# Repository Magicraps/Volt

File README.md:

# Volt
Vehicle Operations and Launch Telemetry - AerospaceNU's rocketry flight controller
https://github.com/AerospaceNU

Currently working on V1.
Open files in KiCAD. (I'm currently using V9.0)

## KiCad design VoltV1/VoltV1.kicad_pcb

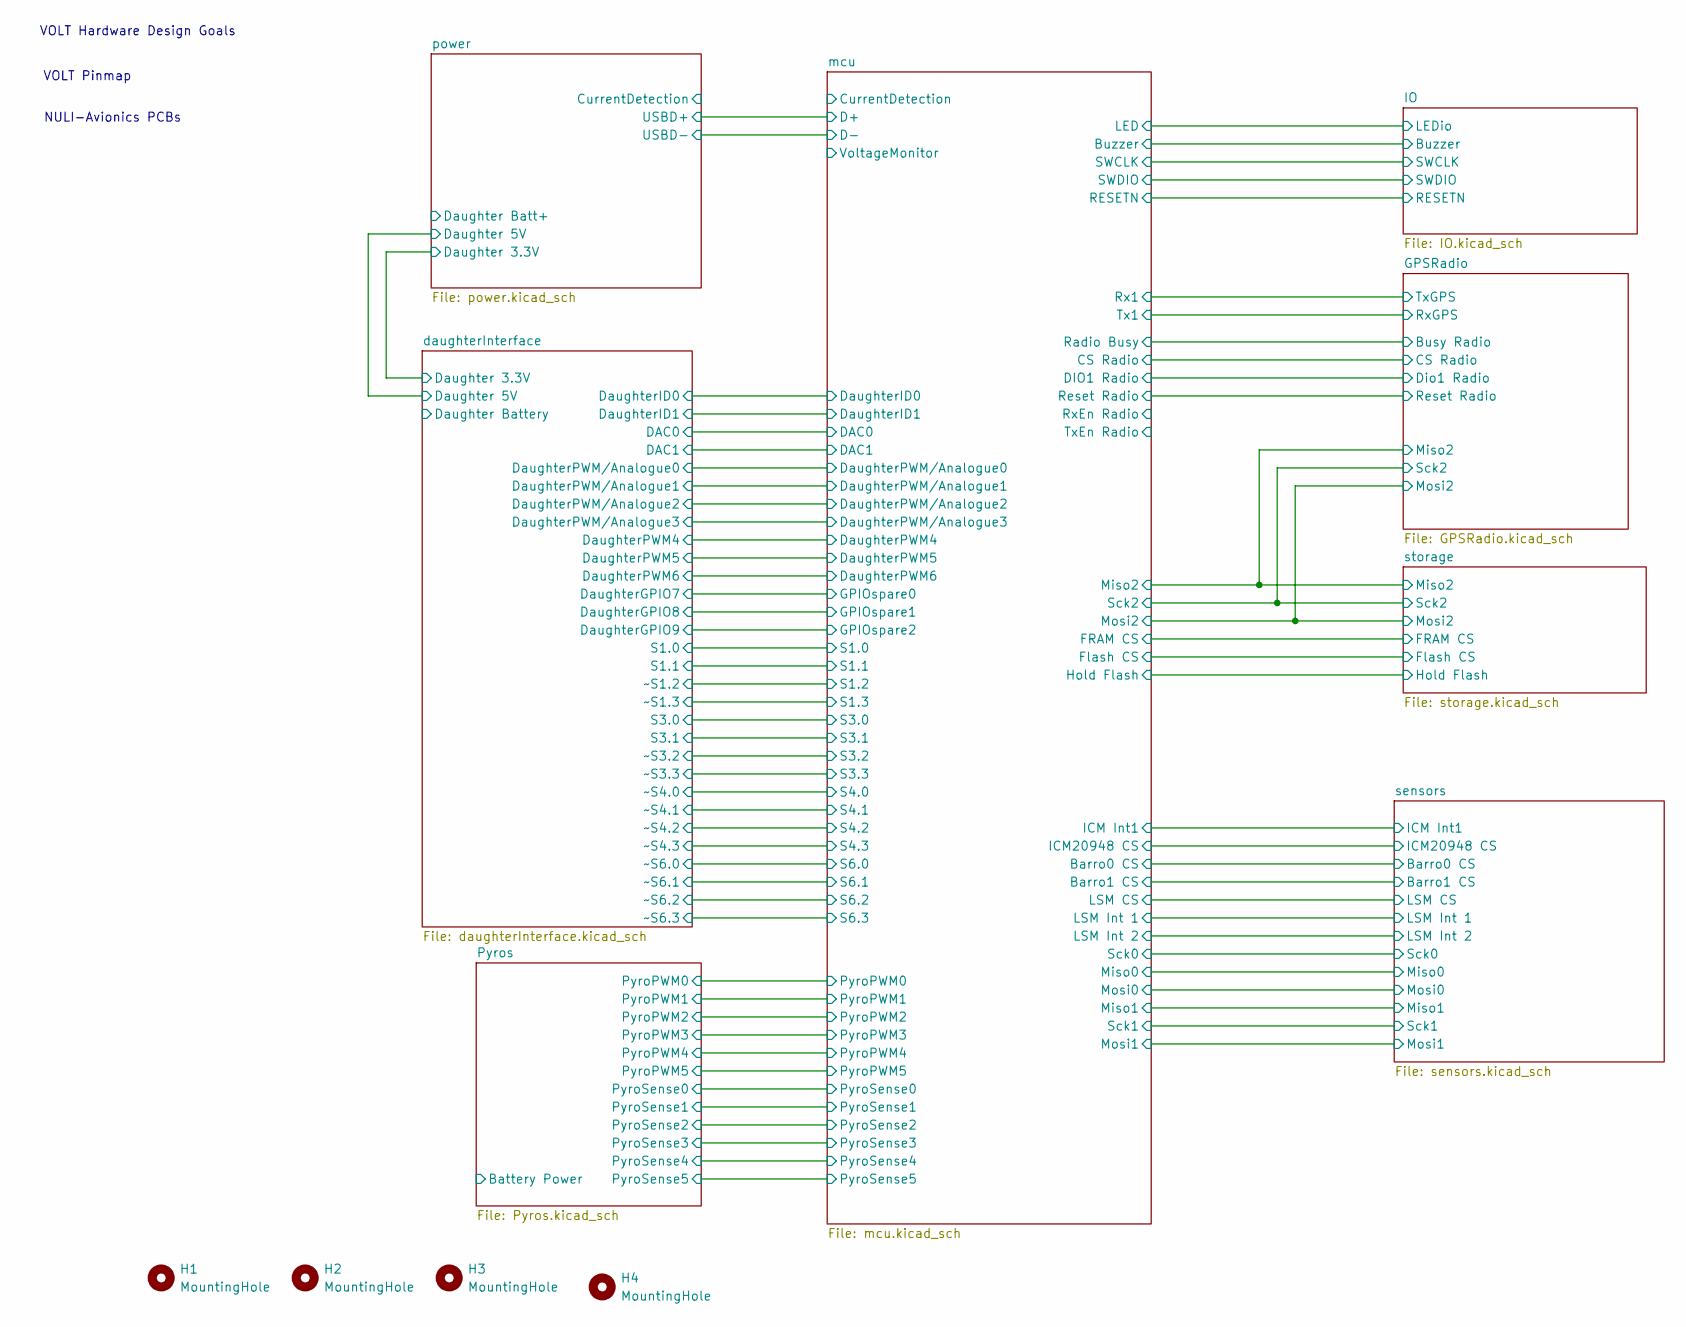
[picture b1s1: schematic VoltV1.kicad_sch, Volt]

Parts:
H1, H2, H3, H4: MountingHole; FixedMountingHole_2.5mm_Pad

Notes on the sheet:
NULI-Avionics PCBs
VOLT Hardware Design Goals
VOLT Pinmap

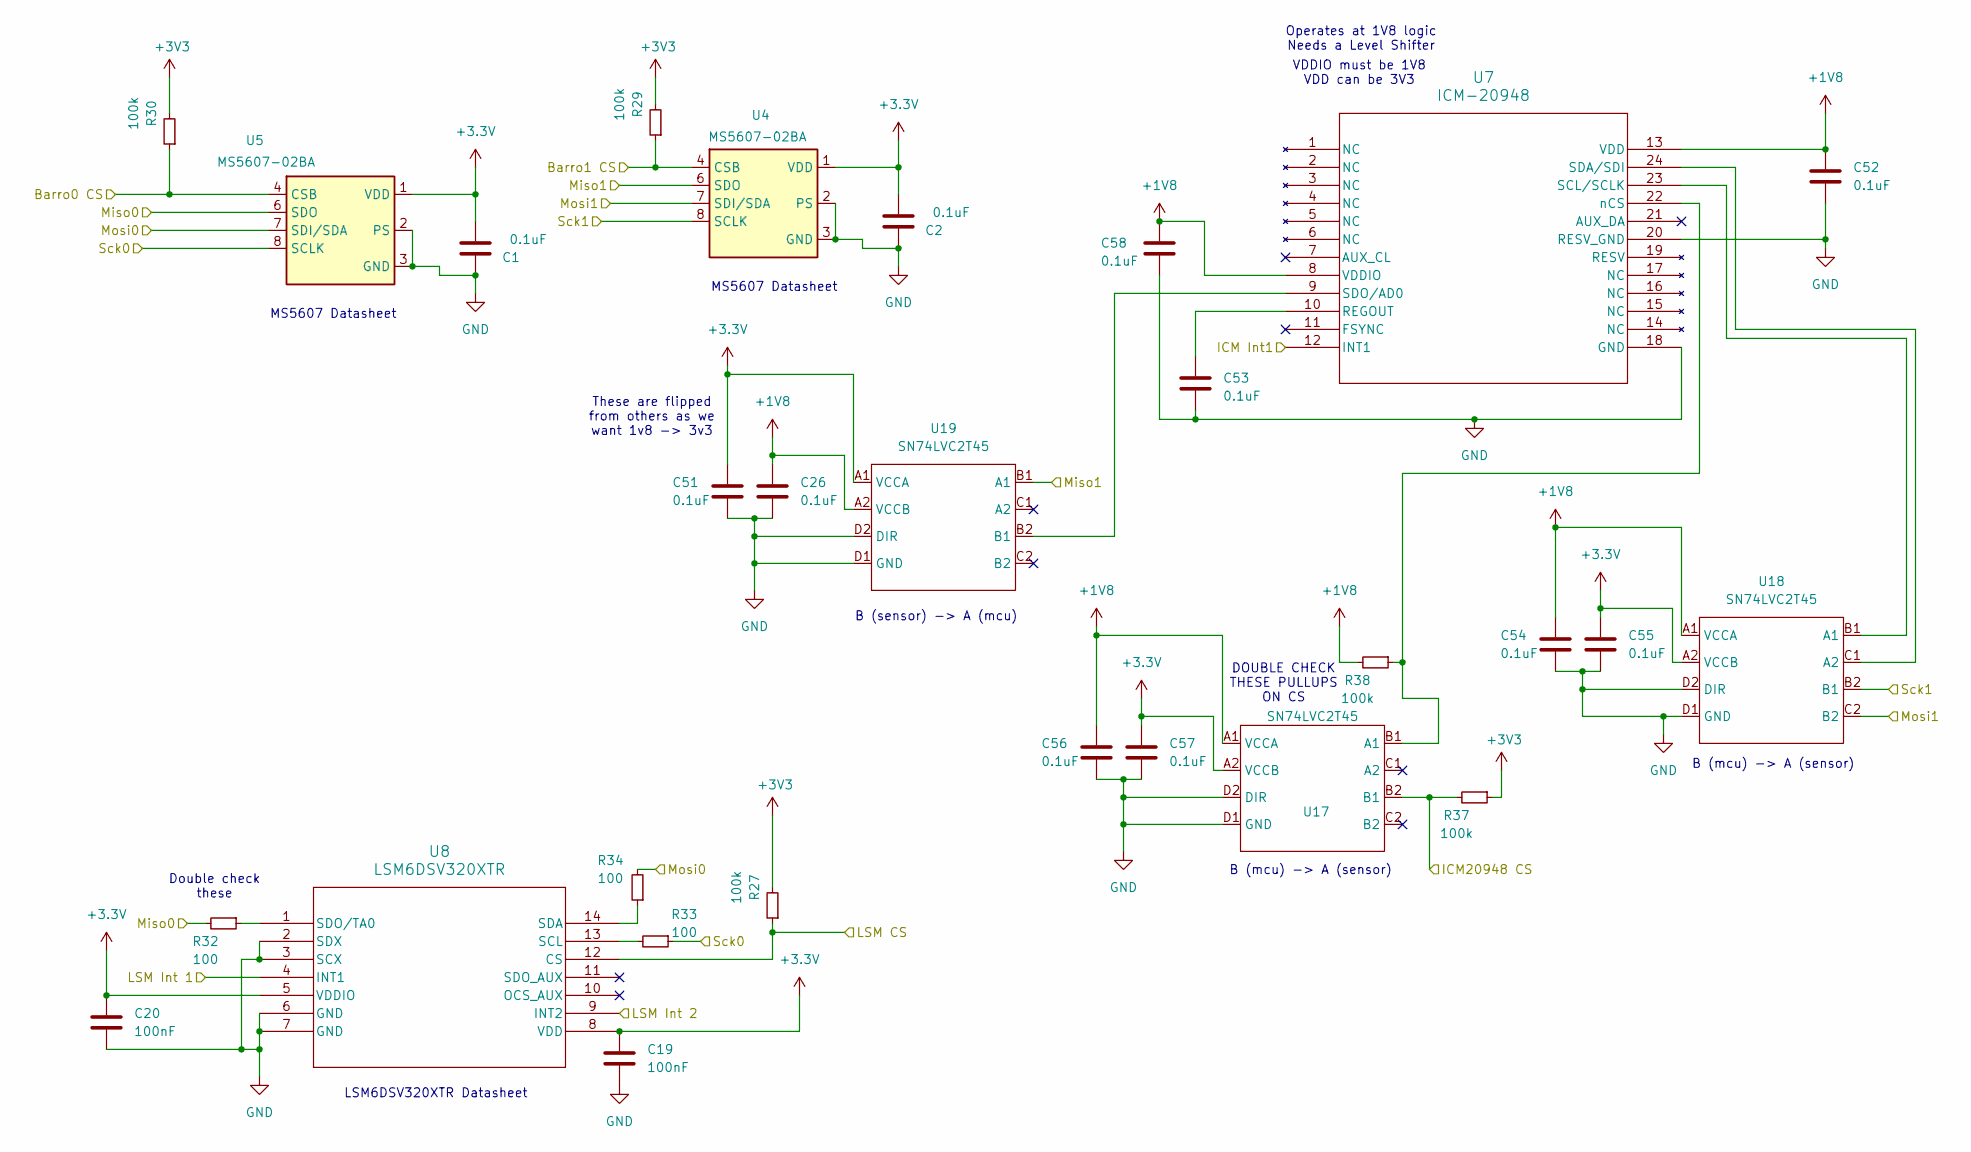
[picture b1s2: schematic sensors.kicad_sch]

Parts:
C1, C2, C26, C51, C52, C53, C54, C55, C56, C57, C58: 0.1uF; C_0402_1005Metric
C19, C20: 100nF; C_0402_1005Metric
R27, R29, R30, R37, R38: 100k; R_0402_1005Metric; LCSC C25077
R32, R33, R34: 100; R_0402_1005Metric; LCSC C25077
U4, U5: MS5607-02BA; LGA-8_3x5mm_P1.25mm
U7: ICM-20948; ICM_20948
U8: LSM6DSV320XTR
U17, U18, U19: SN74LVC2T45; Texas_DSBGA-8_0.9x1.9mm_Layout2x4_P0.5mm

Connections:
+1V8: C26.1, C52.1, C54.1, C56.1, C58.2, R38.2, U7.8 (VDDIO), U7.13 (VDD), U17.A1 (VCCA), U18.A1 (VCCA), U19.A2 (VCCB)
+3.3V: C1.2, C2.2, C19.1, C20.2, C51.1, C55.1, C57.1, U4.1 (VDD), U5.1 (VDD), U8.5 (VDDIO), U8.8 (VDD), U17.A2 (VCCB), U18.A2 (VCCB), U19.A1 (VCCA); also elsewhere on the board
+3V3: R27.2, R29.2, R30.2, R37.1; also elsewhere on the board
/mcu/Barro0 CS: R30.1, U5.4 (CSB); also elsewhere on the board
/mcu/Barro1 CS: R29.1, U4.4 (CSB); also elsewhere on the board
/mcu/ICM20948 CS: R37.2, U17.B2 (B1); also elsewhere on the board
/mcu/ICM Int1: U7.12 (INT1); also elsewhere on the board
/mcu/LSM CS: R27.1, U8.12 (CS); also elsewhere on the board
/mcu/LSM Int 1: U8.4 (INT1); also elsewhere on the board
/mcu/LSM Int 2: U8.9 (INT2); also elsewhere on the board
/mcu/Miso0: R32.2, U5.6 (SDO); also elsewhere on the board
/mcu/Miso1: U4.6 (SDO), U19.B1 (A1); also elsewhere on the board
/mcu/Mosi0: R34.2, U5.7 (SDI/SDA); also elsewhere on the board
/mcu/Mosi1: U4.7 (SDI/SDA), U18.C2 (B2); also elsewhere on the board
/mcu/Sck0: R33.1, U5.8 (SCLK); also elsewhere on the board
/mcu/Sck1: U4.8 (SCLK), U18.B2 (B1); also elsewhere on the board
GND: C1.1, C2.1, C19.2, C20.1, C26.2, C51.2, C52.2, C53.1, C54.2, C55.2, C56.2, C57.2, C58.1, U4.2 (PS), U4.3 (GND), U5.2 (PS), U5.3 (GND), U7.18 (GND), U7.20 (RESV_GND), U8.2 (SDX), U8.3 (SCX), U8.6 (GND), U8.7 (GND), U17.D1 (GND), U17.D2 (DIR), U18.D1 (GND), U18.D2 (DIR), U19.D1 (GND), U19.D2 (DIR); also elsewhere on the board
unnamed: C53.2, U7.10 (REGOUT)
unnamed: R33.2, U8.13 (SCL)
unnamed: R34.1, U8.14 (SDA)
unnamed: R32.1, U8.1 (SDO/TA0)
unnamed: R38.1, U7.22 (nCS), U17.B1 (A1)
unnamed: U7.23 (SCL/SCLK), U18.B1 (A1)
unnamed: U7.24 (SDA/SDI), U18.C1 (A2)
unnamed: U7.9 (SDO/AD0), U19.B2 (B1)

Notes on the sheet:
B (mcu) -> A (sensor)
LSM6DSV320XTR Datasheet
MS5607 Datasheet
VDDIO must be 1V8 VDD can be 3V3
Double check these
DOUBLE CHECK THESE PULLUPS ON CS
B (sensor) -> A (mcu)
These are flipped from others as we want 1v8 -> 3v3
Operates at 1V8 logic Needs a Level Shifter

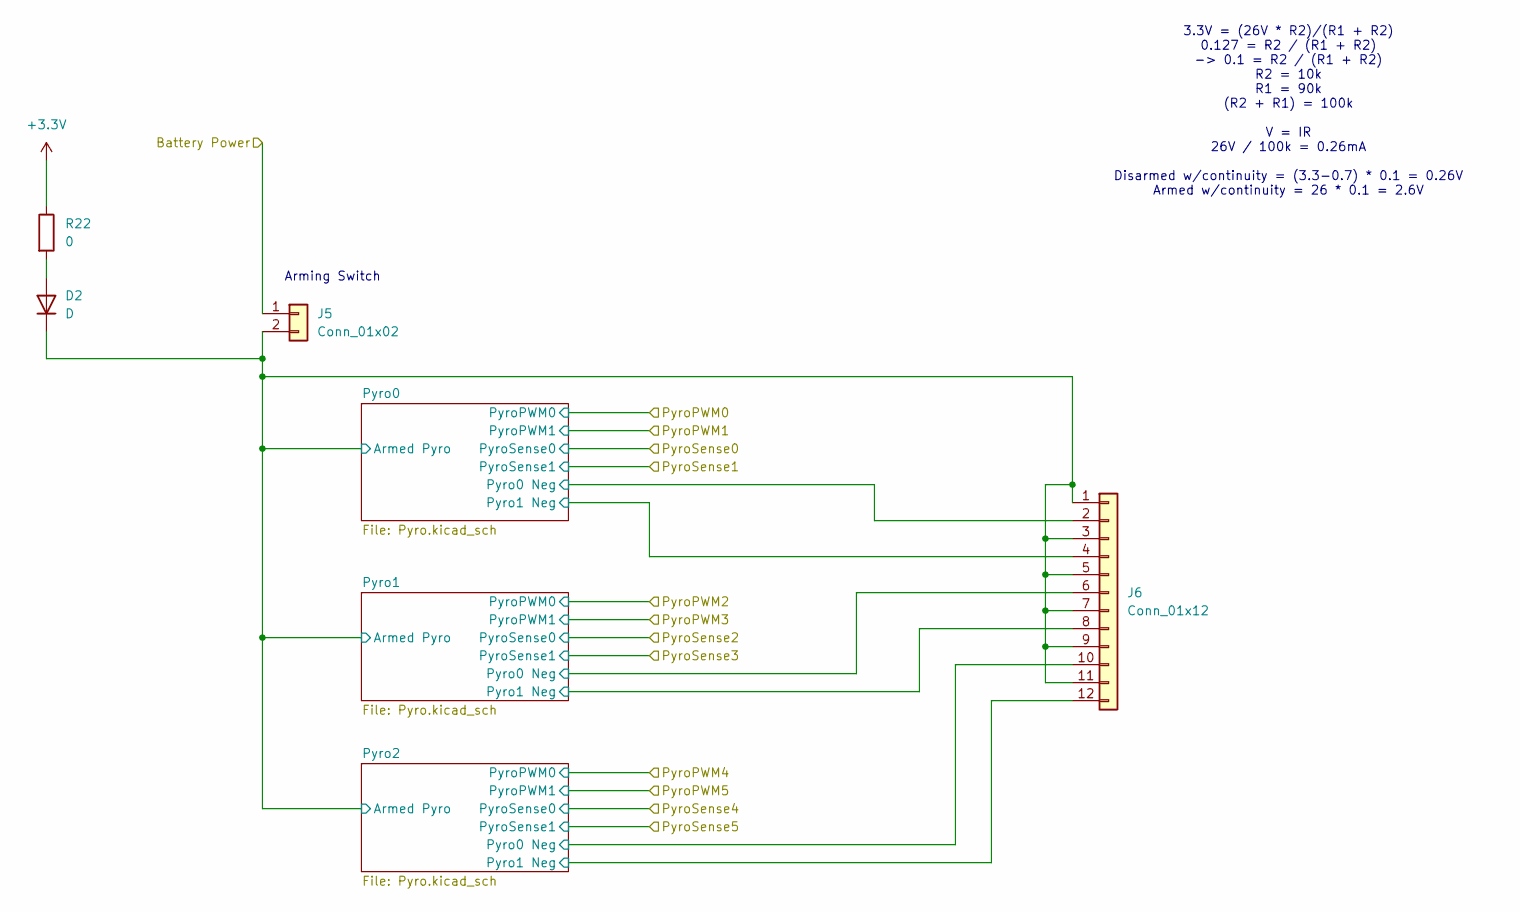
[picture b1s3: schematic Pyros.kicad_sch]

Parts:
D2: D
J5: Conn_01x02
J6: Conn_01x12
R22: 0; R_0402_1005Metric

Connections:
+3.3V: R22.1; also elsewhere on the board
unnamed: D2.2 (A), R22.2
unnamed: D2.1 (K), J5.2, J6.1, J6.3, J6.5, J6.7, J6.9, J6.11

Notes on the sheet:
Arming Switch
3.3V = (26V * R2)/(R1 + R2) 0.127 = R2 / (R1 + R2) -> 0.1 = R2 / (R1 + R2) R2 = 10k R1 = 90k (R2 + R1) = 100k V = IR 26V / 100k = 0.26mA Disarmed w/continuity = (3.3-0.7) * 0.1 = 0.26V Armed w/continuity = 26 * 0.1 = 2.6V

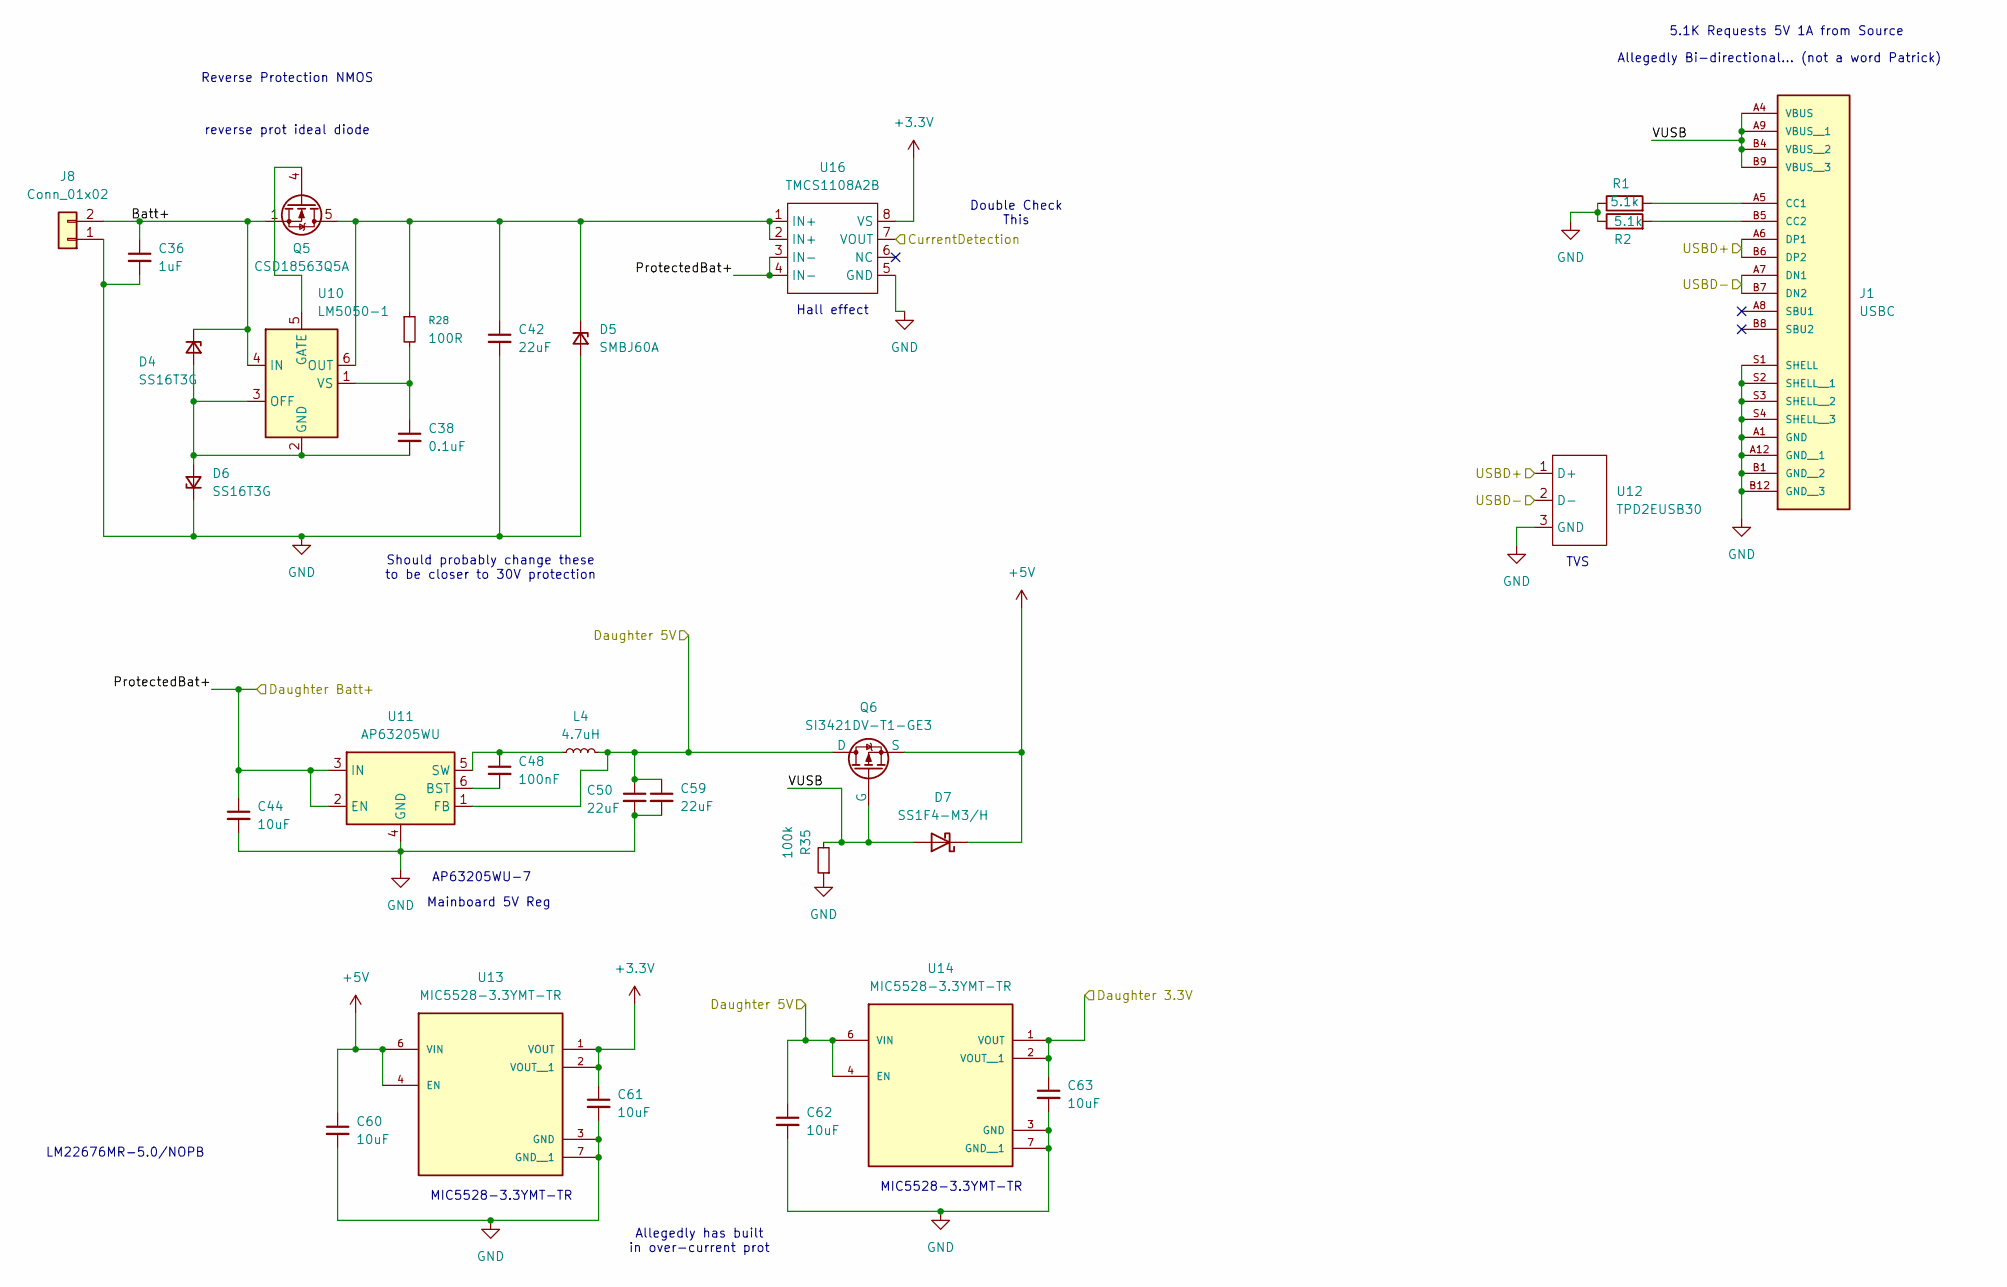
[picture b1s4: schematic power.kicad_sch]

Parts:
C36: 1uF; C_0402_1005Metric
C38: 0.1uF; C_0402_1005Metric
C42, C50, C59: 22uF; C_0402_1005Metric
C44, C60, C61, C62, C63: 10uF; C_0402_1005Metric
C48: 100nF; C_0402_1005Metric
D4, D6: SS16T3G
D5: SMBJ60A
D7: SS1F4-M3/H; D_SOD-123
J1: USBC; PARTREV B
J8: Conn_01x02
L4: 4.7uH; L_0603_1608Metric
Q5: CSD18563Q5A; TDSON-8-1
Q6: SI3421DV-T1-GE3; TSOP-6_1.65x3.05mm_P0.95mm
R1, R2: 5.1k; R_0402_1005Metric
R28: 100R; R_0402_1005Metric
R35: 100k; R_0402_1005Metric; LCSC C25077
U10: LM5050-1; TSOT-23-6
U11: AP63205WU; TSOT-23-6
U12: TPD2EUSB30; Texas_DRT-3
U13, U14: MIC5528-3.3YMT-TR; SON40P120X120X60-7N
U16: TMCS1108A2B; SOIC-8_3.9x4.9mm_P1.27mm

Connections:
+3.3V: C61.1, U13.1 (VOUT), U13.2 (VOUT__1), U16.8 (VS); also elsewhere on the board
+5V: C60.1, D7.1 (K), Q6.4 (S), U13.4 (EN), U13.6 (VIN)
/daughterInterface/Daughter 3.3V: C63.1, U14.1 (VOUT), U14.2 (VOUT__1); also elsewhere on the board
/daughterInterface/Daughter 5V: C50.1, C59.1, C62.1, L4.2, Q6.1 (D), Q6.2 (D), Q6.5 (D), Q6.6 (D), U11.1 (FB), U14.4 (EN), U14.6 (VIN); also elsewhere on the board
/mcu/D+: J1.A6 (DP1), J1.B6 (DP2), U12.1 (D+); also elsewhere on the board
/mcu/D-: J1.A7 (DN1), J1.B7 (DN2), U12.2 (D-); also elsewhere on the board
/power/CurrentDetection: U16.7 (VOUT)
/power/ProtectedBat+: C44.1, U11.2 (EN), U11.3 (IN), U16.3 (IN-), U16.4 (IN-)
/power/VUSB: D7.2 (A), J1.A4 (VBUS), J1.A9 (VBUS__1), J1.B4 (VBUS__2), J1.B9 (VBUS__3), Q6.3 (G), R35.2
GND: C36.2, C42.2, C44.2, C50.2, C59.2, C60.2, C61.2, C62.2, C63.2, D5.2 (A), D6.1 (K), J1.A1 (GND), J1.A12 (GND__1), J1.B1 (GND__2), J1.B12 (GND__3), J1.S1 (SHELL), J1.S2 (SHELL__1), J1.S3 (SHELL__2), J1.S4 (SHELL__3), J8.1, R1.1, R2.1, R35.1, U11.4 (GND), U12.3 (GND), U13.3 (GND), U13.7 (GND__1), U14.3 (GND), U14.7 (GND__1), U16.5 (GND); also elsewhere on the board
unnamed: C38.2, D4.2 (A), D6.2 (A), U10.2 (GND), U10.3 (OFF)
unnamed: J1.A5 (CC1), R1.2
unnamed: J1.B5 (CC2), R2.2
unnamed: Q5.4 (G), U10.5 (GATE)
unnamed: C38.1, R28.2, U10.1 (VS)
unnamed: C48.2, U11.6 (BST)
unnamed: C48.1, L4.1, U11.5 (SW)

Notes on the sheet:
LM22676MR-5.0/NOPB
Double Check This
Should probably change these to be closer to 30V protection
Reverse Protection NMOS
TVS
Allegedly has built in over-current prot
Hall effect
MIC5528-3.3YMT-TR
Allegedly Bi-directional... (not a word Patrick)
Mainboard 5V Reg
reverse prot ideal diode
5.1K Requests 5V 1A from Source
AP63205WU-7

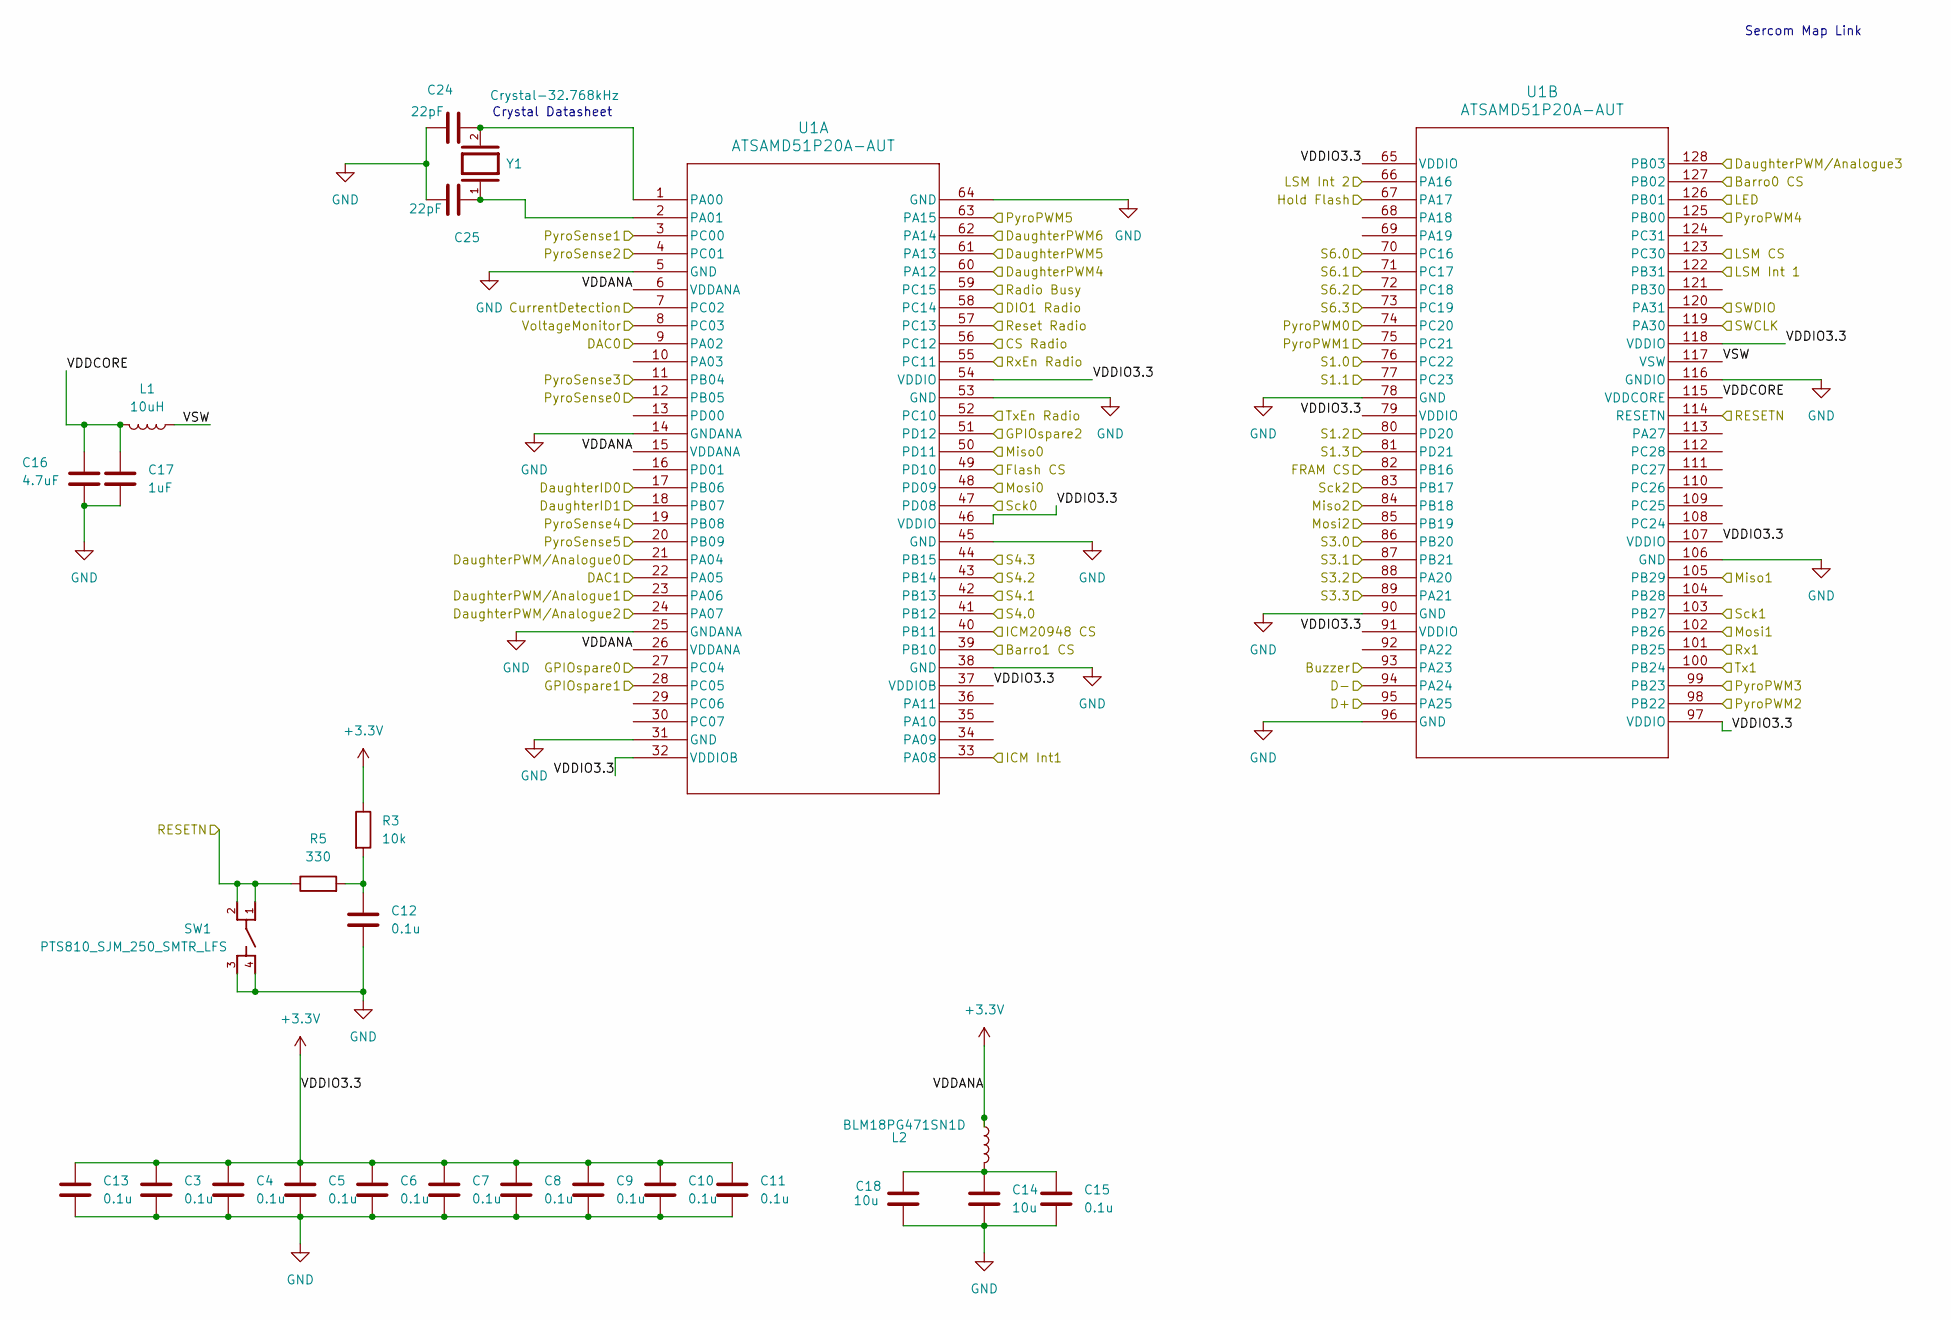
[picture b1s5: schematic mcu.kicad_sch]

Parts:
C3, C4, C5, C6, C7, C8, C9, C10, C11, C12, C13, C15: 0.1u; C_0402_1005Metric
C14, C18: 10u; C_0402_1005Metric
C16: 4.7uF; C_0402_1005Metric
C17: 1uF; C_0402_1005Metric
C24, C25: 22pF; C_0402_1005Metric
L1: 10uH; L_0603_1608Metric
L2: BLM18PG471SN1D; L_0603_1608Metric
R3: 10k; R_0402_1005Metric
R5: 330; R_0402_1005Metric
SW1: PTS810_SJM_250_SMTR_LFS; SW_PTS810_SJM_250_SMTR_LFS
U1: ATSAMD51P20A-AUT
Y1: Crystal-32.768kHz; XTAL_ABS07-32.768KHZ-T; PARTREV 08.19.15

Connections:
+3.3V: C3.1, C4.1, C5.1, C6.1, C7.1, C8.1, C9.1, C10.1, C11.1, C13.1, L2.1, R3.1, U1.6 (VDDANA), U1.15 (VDDANA), U1.26 (VDDANA), U1.32 (VDDIOB), U1.37 (VDDIOB), U1.46 (VDDIO), U1.54 (VDDIO), U1.65 (VDDIO), U1.79 (VDDIO), U1.91 (VDDIO), U1.97 (VDDIO), U1.107 (VDDIO), U1.118 (VDDIO); also elsewhere on the board
/GPSRadio/Busy Radio: U1.59 (PC15); also elsewhere on the board
/GPSRadio/CS Radio: U1.56 (PC12); also elsewhere on the board
/GPSRadio/Dio1 Radio: U1.58 (PC14); also elsewhere on the board
/GPSRadio/Miso2: U1.84 (PB18); also elsewhere on the board
/GPSRadio/Mosi2: U1.85 (PB19); also elsewhere on the board
/GPSRadio/Reset Radio: U1.57 (PC13); also elsewhere on the board
/GPSRadio/RxGPS: U1.100 (PB24); also elsewhere on the board
/GPSRadio/Sck2: U1.83 (PB17); also elsewhere on the board
/GPSRadio/TxGPS: U1.101 (PB25); also elsewhere on the board
/IO/Buzzer: U1.93 (PA23); also elsewhere on the board
/IO/LEDio: U1.126 (PB01); also elsewhere on the board
/IO/RESETN: R5.1, SW1.1, SW1.2, U1.114 (RESETN); also elsewhere on the board
/IO/SWCLK: U1.119 (PA30); also elsewhere on the board
/IO/SWDIO: U1.120 (PA31); also elsewhere on the board
/Pyros/PyroPWM0: U1.74 (PC20); also elsewhere on the board
/Pyros/PyroPWM1: U1.75 (PC21); also elsewhere on the board
/Pyros/PyroPWM2: U1.98 (PB22); also elsewhere on the board
/Pyros/PyroPWM3: U1.99 (PB23); also elsewhere on the board
/Pyros/PyroPWM4: U1.125 (PB00); also elsewhere on the board
/Pyros/PyroPWM5: U1.63 (PA15); also elsewhere on the board
/Pyros/PyroSense0: U1.12 (PB05); also elsewhere on the board
/Pyros/PyroSense1: U1.3 (PC00); also elsewhere on the board
/Pyros/PyroSense2: U1.4 (PC01); also elsewhere on the board
/Pyros/PyroSense3: U1.11 (PB04); also elsewhere on the board
/Pyros/PyroSense4: U1.19 (PB08); also elsewhere on the board
/Pyros/PyroSense5: U1.20 (PB09); also elsewhere on the board
/daughterInterface/DAC0: U1.9 (PA02); also elsewhere on the board
/daughterInterface/DAC1: U1.22 (PA05); also elsewhere on the board
/daughterInterface/DaughterGPIO7: U1.27 (PC04); also elsewhere on the board
/daughterInterface/DaughterGPIO8: U1.28 (PC05); also elsewhere on the board
/daughterInterface/DaughterGPIO9: U1.51 (PD12); also elsewhere on the board
/daughterInterface/DaughterID0: U1.17 (PB06); also elsewhere on the board
/daughterInterface/DaughterID1: U1.18 (PB07); also elsewhere on the board
/daughterInterface/DaughterPWM4: U1.60 (PA12); also elsewhere on the board
/daughterInterface/DaughterPWM5: U1.61 (PA13); also elsewhere on the board
/daughterInterface/DaughterPWM6: U1.62 (PA14); also elsewhere on the board
/daughterInterface/DaughterPWM/Analogue0: U1.21 (PA04); also elsewhere on the board
/daughterInterface/DaughterPWM/Analogue1: U1.23 (PA06); also elsewhere on the board
/daughterInterface/DaughterPWM/Analogue2: U1.24 (PA07); also elsewhere on the board
/daughterInterface/DaughterPWM/Analogue3: U1.128 (PB03); also elsewhere on the board
/daughterInterface/S1.0: U1.76 (PC22); also elsewhere on the board
/daughterInterface/S1.1: U1.77 (PC23); also elsewhere on the board
/daughterInterface/S3.0: U1.86 (PB20); also elsewhere on the board
/daughterInterface/S3.1: U1.87 (PB21); also elsewhere on the board
/daughterInterface/~S1.2: U1.80 (PD20); also elsewhere on the board
/daughterInterface/~S1.3: U1.81 (PD21); also elsewhere on the board
/daughterInterface/~S3.2: U1.88 (PA20); also elsewhere on the board
/daughterInterface/~S3.3: U1.89 (PA21); also elsewhere on the board
/daughterInterface/~S4.0: U1.41 (PB12); also elsewhere on the board
/daughterInterface/~S4.1: U1.42 (PB13); also elsewhere on the board
/daughterInterface/~S4.2: U1.43 (PB14); also elsewhere on the board
/daughterInterface/~S4.3: U1.44 (PB15); also elsewhere on the board
/daughterInterface/~S6.0: U1.70 (PC16); also elsewhere on the board
/daughterInterface/~S6.1: U1.71 (PC17); also elsewhere on the board
/daughterInterface/~S6.2: U1.72 (PC18); also elsewhere on the board
/daughterInterface/~S6.3: U1.73 (PC19); also elsewhere on the board
/mcu/Barro0 CS: U1.127 (PB02); also elsewhere on the board
/mcu/Barro1 CS: U1.39 (PB10); also elsewhere on the board
/mcu/CurrentDetection: U1.7 (PC02)
/mcu/D+: U1.95 (PA25); also elsewhere on the board
/mcu/D-: U1.94 (PA24); also elsewhere on the board
/mcu/FRAM CS: U1.82 (PB16); also elsewhere on the board
/mcu/Flash CS: U1.49 (PD10); also elsewhere on the board
/mcu/Hold Flash: U1.67 (PA17); also elsewhere on the board
/mcu/ICM20948 CS: U1.40 (PB11); also elsewhere on the board
/mcu/ICM Int1: U1.33 (PA08); also elsewhere on the board
/mcu/LSM CS: U1.123 (PC30); also elsewhere on the board
/mcu/LSM Int 1: U1.122 (PB31); also elsewhere on the board
/mcu/LSM Int 2: U1.66 (PA16); also elsewhere on the board
/mcu/Miso0: U1.50 (PD11); also elsewhere on the board
/mcu/Miso1: U1.105 (PB29); also elsewhere on the board
/mcu/Mosi0: U1.48 (PD09); also elsewhere on the board
/mcu/Mosi1: U1.102 (PB26); also elsewhere on the board
/mcu/RxEn Radio: U1.55 (PC11)
/mcu/Sck0: U1.47 (PD08); also elsewhere on the board
/mcu/Sck1: U1.103 (PB27); also elsewhere on the board
/mcu/TxEn Radio: U1.52 (PC10)
/mcu/VDDCORE: C16.1, C17.1, L1.2, U1.115 (VDDCORE)
/mcu/VSW: L1.1, U1.117 (VSW)
/mcu/VoltageMonitor: U1.8 (PC03)
GND: C3.2, C4.2, C5.2, C6.2, C7.2, C8.2, C9.2, C10.2, C11.2, C12.2, C13.2, C14.2, C15.2, C16.2, C17.2, C18.2, C24.2, C25.2, SW1.3, SW1.4, U1.5 (GND), U1.14 (GNDANA), U1.25 (GNDANA), U1.31 (GND), U1.38 (GND), U1.45 (GND), U1.53 (GND), U1.64 (GND), U1.78 (GND), U1.90 (GND), U1.96 (GND), U1.106 (GND), U1.116 (GNDIO); also elsewhere on the board
unnamed: C12.1, R3.2, R5.2
unnamed: C14.1, C15.1, C18.1, L2.2
unnamed: C24.1, U1.1 (PA00), Y1.2
unnamed: C25.1, U1.2 (PA01), Y1.1

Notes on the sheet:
Crystal Datasheet
Sercom Map Link

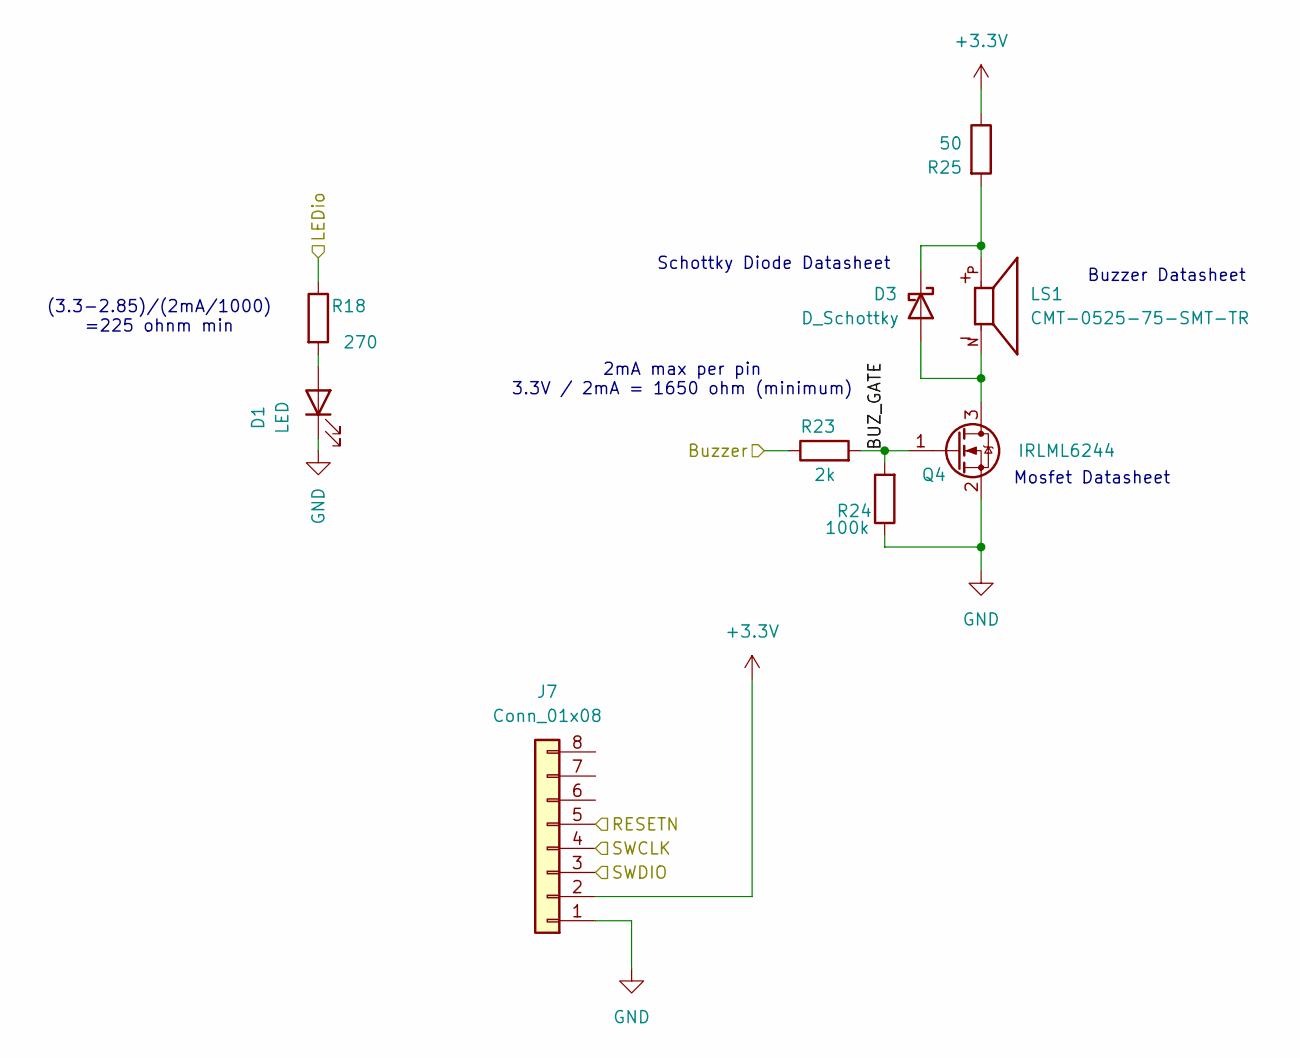
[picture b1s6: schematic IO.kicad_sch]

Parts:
D1: LED; LED_0603_1608Metric
D3: D_Schottky; D_SOD-123
J7: Conn_01x08; JST_GH_BM08B-GHS-TBT_1x08-1MP_P1.25mm_Vertical
LS1: CMT-0525-75-SMT-TR; XDCR_CMT-0525-75-SMT-TR; PARTREV 1.0
Q4: IRLML6244; SOT-23
R18: 270; R_0402_1005Metric
R23: 2k; R_0402_1005Metric
R24: 100k; R_0402_1005Metric
R25: 50; R_0402_1005Metric

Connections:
+3.3V: J7.2, R25.1; also elsewhere on the board
/IO/BUZ_GATE: Q4.1 (G), R23.2, R24.2
/IO/Buzzer: R23.1; also elsewhere on the board
/IO/LEDio: R18.1; also elsewhere on the board
/IO/RESETN: J7.5; also elsewhere on the board
/IO/SWCLK: J7.4; also elsewhere on the board
/IO/SWDIO: J7.3; also elsewhere on the board
GND: D1.1 (K), J7.1, Q4.2 (S), R24.1; also elsewhere on the board
unnamed: D1.2 (A), R18.2
unnamed: D3.2 (A), LS1.N, Q4.3 (D)
unnamed: D3.1 (K), LS1.P, R25.2

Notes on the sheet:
Buzzer Datasheet
Schottky Diode Datasheet
(3.3-2.85)/(2mA/1000) =225 ohnm min
Mosfet Datasheet
2mA max per pin 3.3V / 2mA = 1650 ohm (minimum)

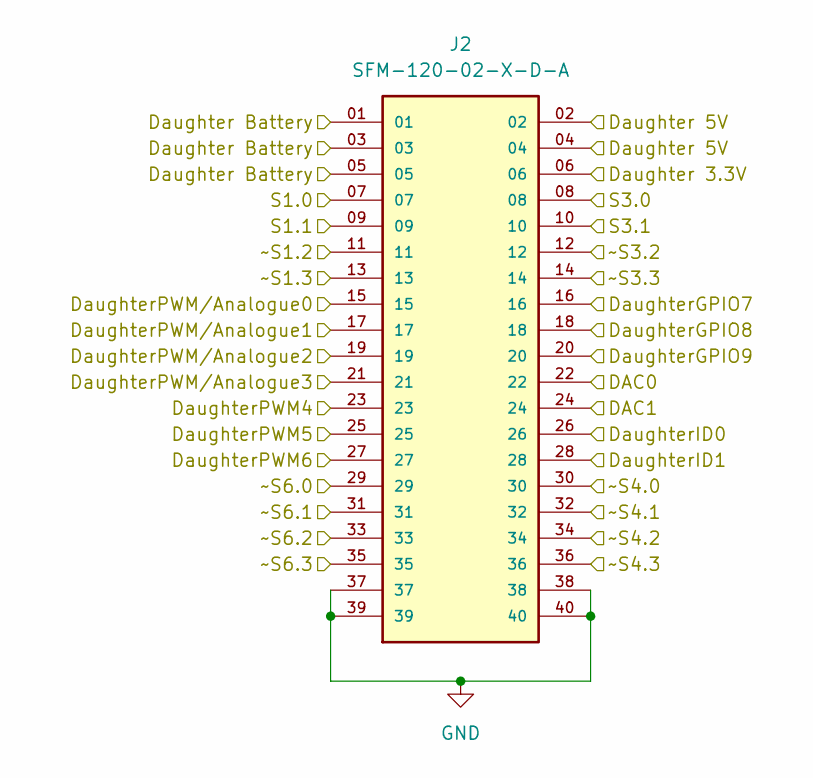
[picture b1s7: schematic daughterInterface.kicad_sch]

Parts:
J2: SFM-120-02-X-D-A; SAMTEC_SFM-120-02-X-D-A; PARTREV Q

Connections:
/daughterInterface/DAC0: J2.22; also elsewhere on the board
/daughterInterface/DAC1: J2.24; also elsewhere on the board
/daughterInterface/Daughter 3.3V: J2.06; also elsewhere on the board
/daughterInterface/Daughter 5V: J2.02, J2.04; also elsewhere on the board
/daughterInterface/Daughter Battery: J2.01, J2.03, J2.05
/daughterInterface/DaughterGPIO7: J2.16; also elsewhere on the board
/daughterInterface/DaughterGPIO8: J2.18; also elsewhere on the board
/daughterInterface/DaughterGPIO9: J2.20; also elsewhere on the board
/daughterInterface/DaughterID0: J2.26; also elsewhere on the board
/daughterInterface/DaughterID1: J2.28; also elsewhere on the board
/daughterInterface/DaughterPWM4: J2.23; also elsewhere on the board
/daughterInterface/DaughterPWM5: J2.25; also elsewhere on the board
/daughterInterface/DaughterPWM6: J2.27; also elsewhere on the board
/daughterInterface/DaughterPWM/Analogue0: J2.15; also elsewhere on the board
/daughterInterface/DaughterPWM/Analogue1: J2.17; also elsewhere on the board
/daughterInterface/DaughterPWM/Analogue2: J2.19; also elsewhere on the board
/daughterInterface/DaughterPWM/Analogue3: J2.21; also elsewhere on the board
/daughterInterface/S1.0: J2.07; also elsewhere on the board
/daughterInterface/S1.1: J2.09; also elsewhere on the board
/daughterInterface/S3.0: J2.08; also elsewhere on the board
/daughterInterface/S3.1: J2.10; also elsewhere on the board
/daughterInterface/~S1.2: J2.11; also elsewhere on the board
/daughterInterface/~S1.3: J2.13; also elsewhere on the board
/daughterInterface/~S3.2: J2.12; also elsewhere on the board
/daughterInterface/~S3.3: J2.14; also elsewhere on the board
/daughterInterface/~S4.0: J2.30; also elsewhere on the board
/daughterInterface/~S4.1: J2.32; also elsewhere on the board
/daughterInterface/~S4.2: J2.34; also elsewhere on the board
/daughterInterface/~S4.3: J2.36; also elsewhere on the board
/daughterInterface/~S6.0: J2.29; also elsewhere on the board
/daughterInterface/~S6.1: J2.31; also elsewhere on the board
/daughterInterface/~S6.2: J2.33; also elsewhere on the board
/daughterInterface/~S6.3: J2.35; also elsewhere on the board
GND: J2.37, J2.38, J2.39, J2.40; also elsewhere on the board
